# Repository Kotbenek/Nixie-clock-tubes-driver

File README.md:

# Moved to Codeberg

This repository was moved to Codeberg:
https://codeberg.org/Kotbenek/Nixie-clock-tubes-driver

# Nixie-clock-tubes-driver
PCB responsible for driving Nixie tubes

## Board overview

- 6P6C connector used for interfacing the [Nixie clock main board](https://github.com/Kotbenek/Nixie-clock-main-board)
- 180V DC input (powered by [180V power supply](https://github.com/Kotbenek/180V-power-supply))
- 6 11-pin connectors for 6 Nixie tubes:
  - 10 cathode pins, statically driving each digit
  - 1 anode pin, with dimming capability (PWM)

## Images

## External 3D models used in the PCB render

- [6P6C connector](https://grabcad.com/library/rj12-1)

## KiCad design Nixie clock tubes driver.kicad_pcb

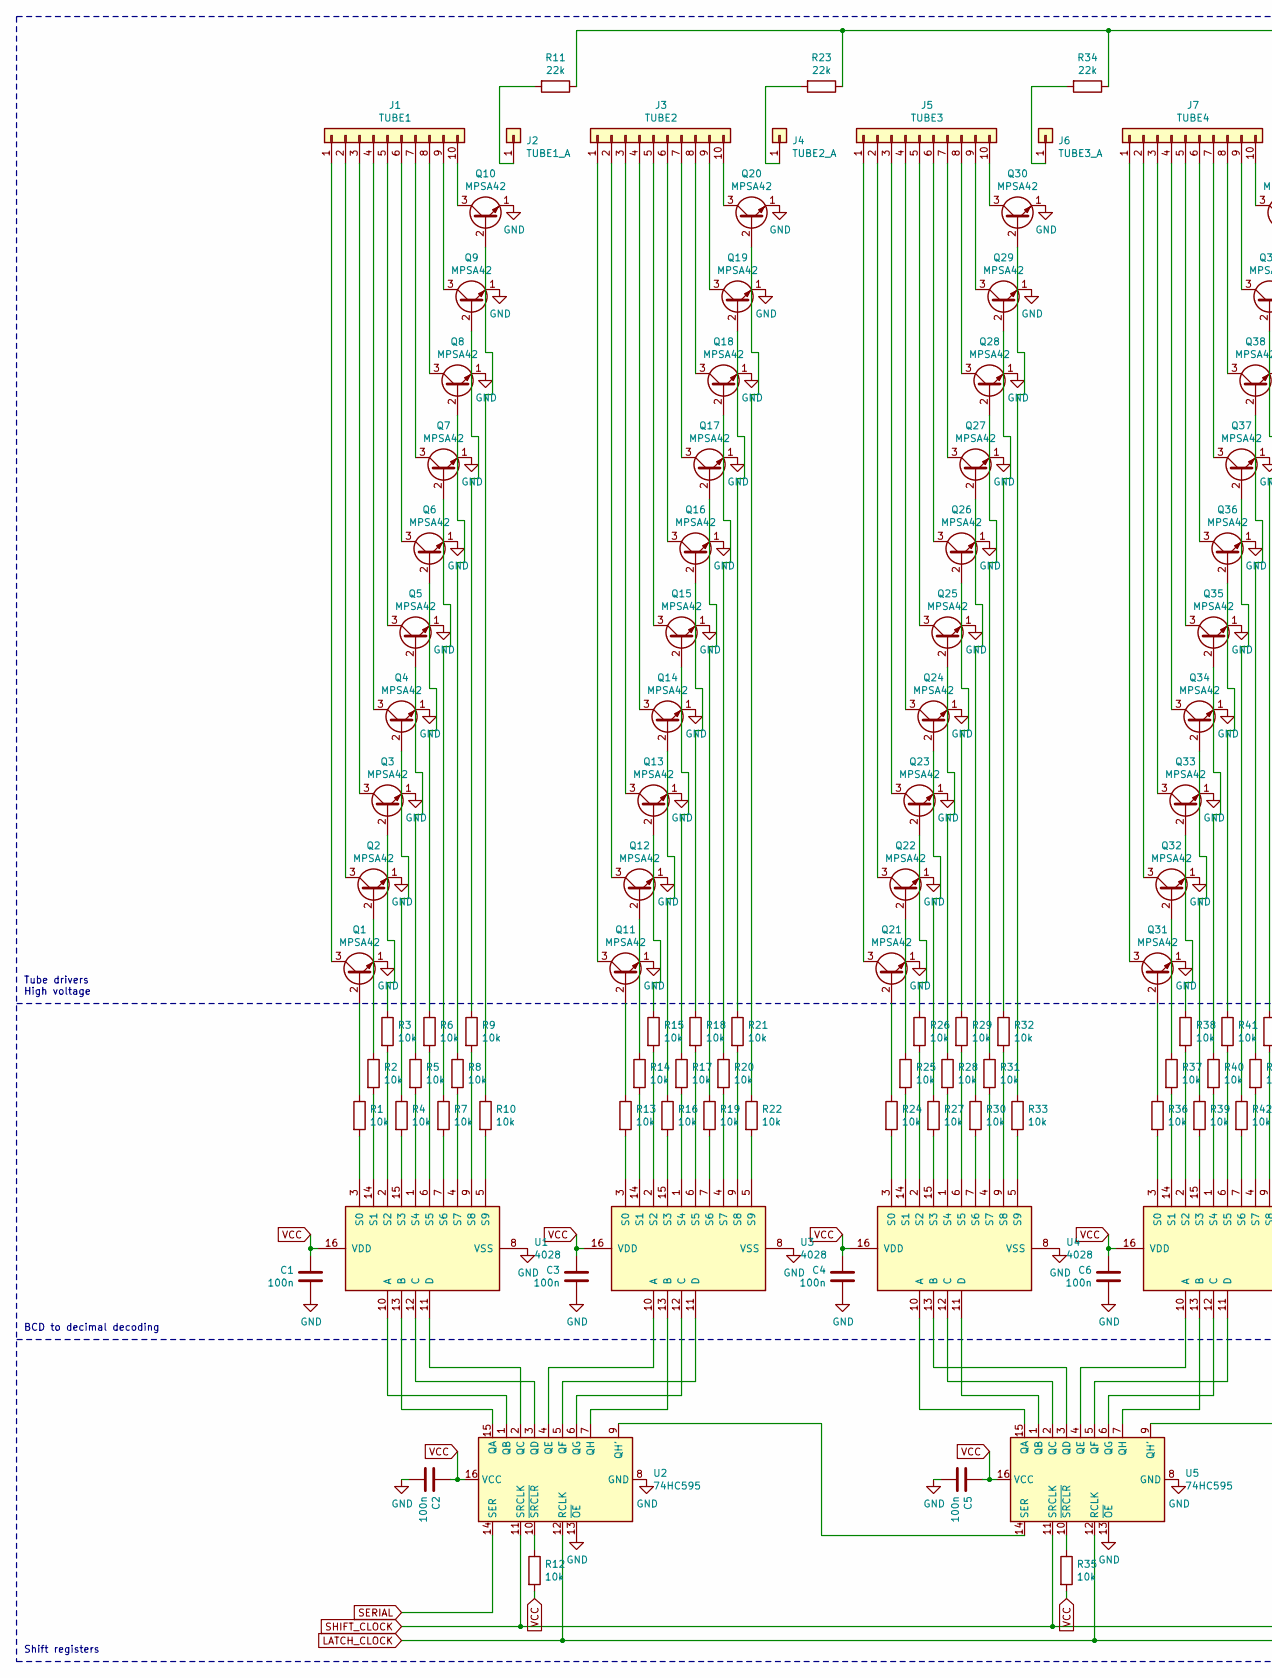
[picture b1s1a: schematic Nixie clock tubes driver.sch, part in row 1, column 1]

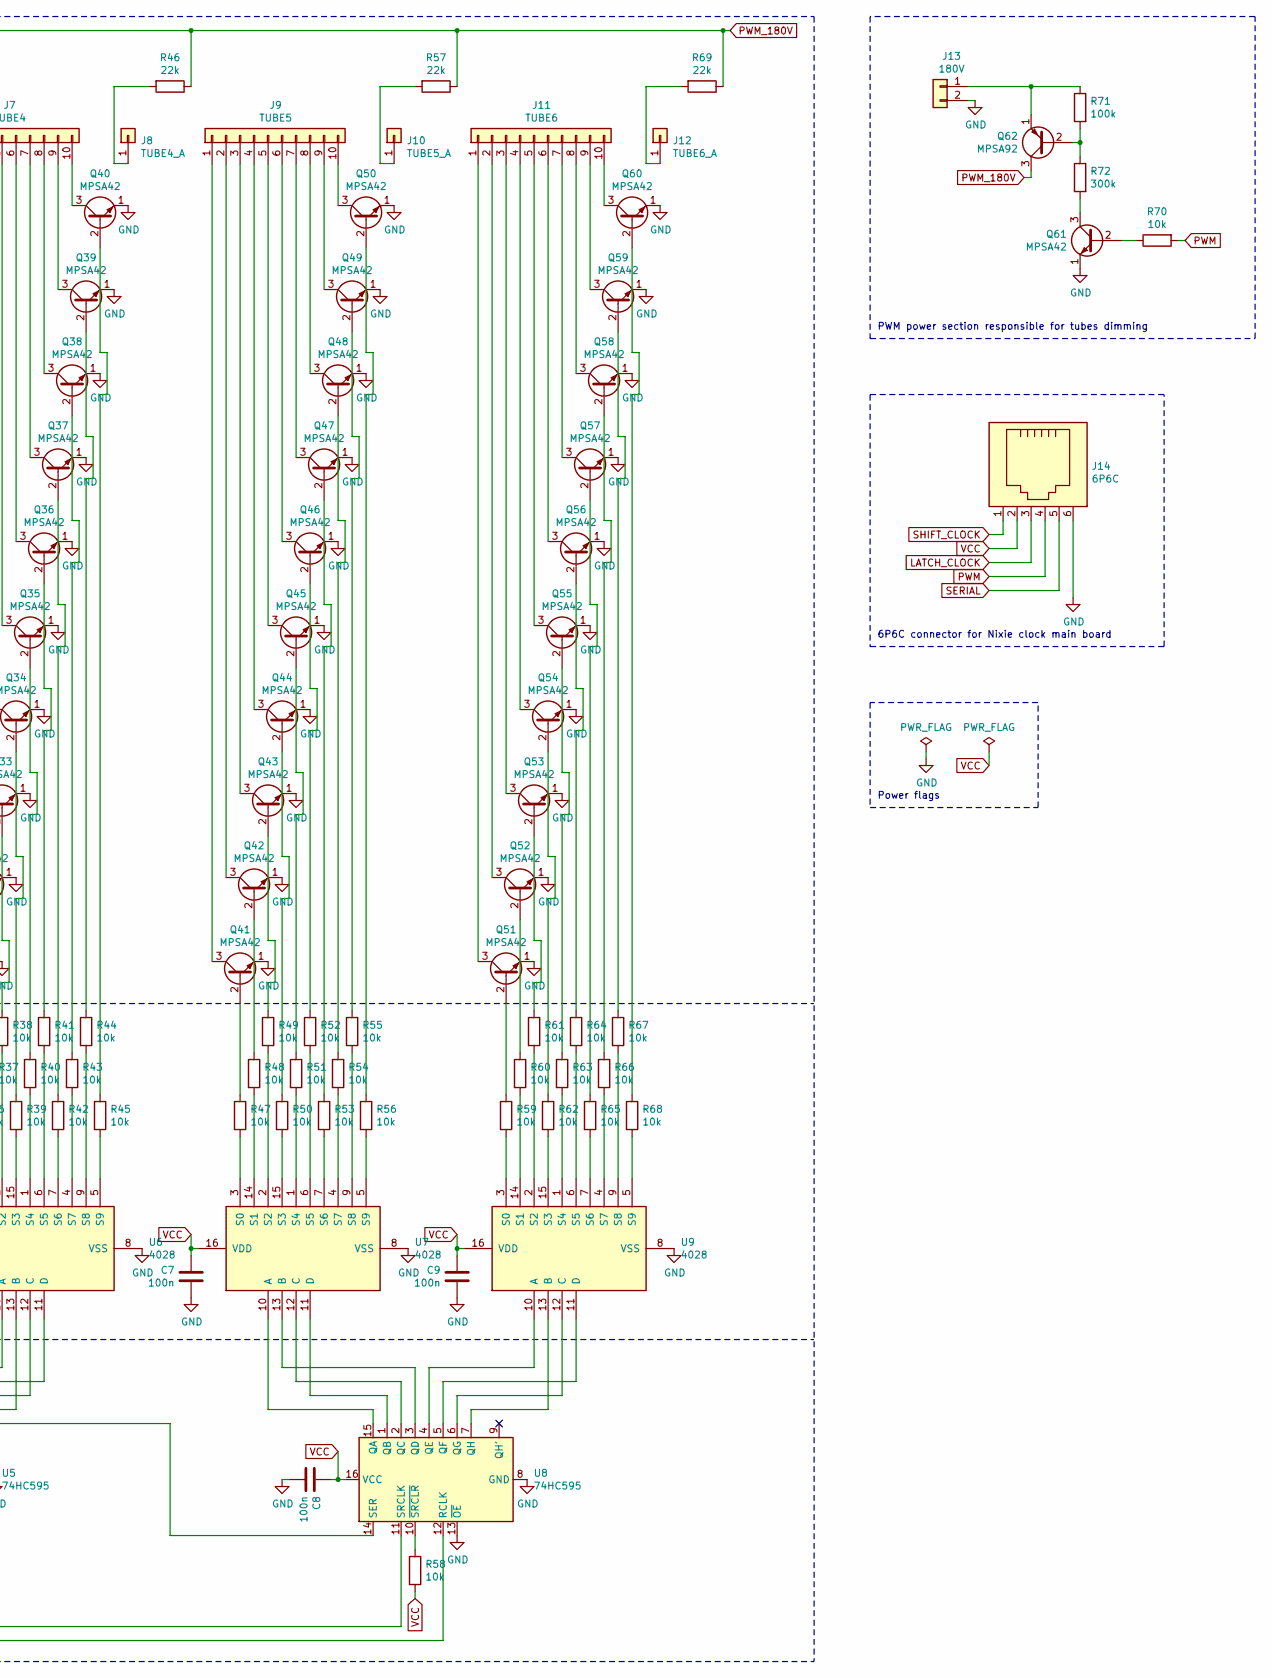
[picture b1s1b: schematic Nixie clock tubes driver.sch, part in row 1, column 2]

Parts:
C1, C2, C3, C4, C5, C6, C7, C8, C9: 100n; C_0805_2012Metric
J1: TUBE1; PinHeader_1x10_P2.54mm_Vertical
J2: TUBE1_A; PinHeader_1x01_P2.54mm_Vertical
J3: TUBE2; PinHeader_1x10_P2.54mm_Vertical
J4: TUBE2_A; PinHeader_1x01_P2.54mm_Vertical
J5: TUBE3; PinHeader_1x10_P2.54mm_Vertical
J6: TUBE3_A; PinHeader_1x01_P2.54mm_Vertical
J7: TUBE4; PinHeader_1x10_P2.54mm_Vertical
J8: TUBE4_A; PinHeader_1x01_P2.54mm_Vertical
J9: TUBE5; PinHeader_1x10_P2.54mm_Vertical
J10: TUBE5_A; PinHeader_1x01_P2.54mm_Vertical
J11: TUBE6; PinHeader_1x10_P2.54mm_Vertical
J12: TUBE6_A; PinHeader_1x01_P2.54mm_Vertical
J13: 180V; PinHeader_1x02_P2.54mm_Vertical
J14: 6P6C; RJ12_Amphenol_54601
Q1, Q2, Q3, Q4, Q5, Q6, Q7, Q8, Q9, Q10, Q11, Q12, Q13, Q14, Q15, Q16, Q17, Q18, Q19, Q20, Q21, Q22, Q23, Q24, Q25, Q26, Q27, Q28, Q29, Q30, Q31, Q32, Q33, Q34, Q35, Q36, Q37, Q38, Q39, Q40, Q41, Q42, Q43, Q44, Q45, Q46, Q47, Q48, Q49, Q50, Q51, Q52, Q53, Q54, Q55, Q56, Q57, Q58, Q59, Q60, Q61: MPSA42; TO-92_Inline
Q62: MPSA92; TO-92_Inline
R1, R2, R3, R4, R5, R6, R7, R8, R9, R10, R12, R13, R14, R15, R16, R17, R18, R19, R20, R21, R22, R24, R25, R26, R27, R28, R29, R30, R31, R32, R33, R35, R36, R37, R38, R39, R40, R41, R42, R43, R44, R45, R47, R48, R49, R50, R51, R52, R53, R54, R55, R56, R58, R59, R60, R61, R62, R63, R64, R65, R66, R67, R68, R70: 10k; R_0805_2012Metric
R11, R23, R34, R46, R57, R69: 22k; R_1206_3216Metric
R71: 100k; R_1206_3216Metric
R72: 300k; R_1206_3216Metric
U1, U3, U4, U6, U7, U9: 4028; SOIC-16_4.55x10.3mm_P1.27mm
U2, U5, U8: 74HC595; SOIC-16_4.55x10.3mm_P1.27mm

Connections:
GND: C1.2, C2.2, C3.2, C4.2, C5.2, C6.2, C7.2, C8.2, C9.2, J13.2, J14.6, Q1.1 (E), Q2.1 (E), Q3.1 (E), Q4.1 (E), Q5.1 (E), Q6.1 (E), Q7.1 (E), Q8.1 (E), Q9.1 (E), Q10.1 (E), Q11.1 (E), Q12.1 (E), Q13.1 (E), Q14.1 (E), Q15.1 (E), Q16.1 (E), Q17.1 (E), Q18.1 (E), Q19.1 (E), Q20.1 (E), Q21.1 (E), Q22.1 (E), Q23.1 (E), Q24.1 (E), Q25.1 (E), Q26.1 (E), Q27.1 (E), Q28.1 (E), Q29.1 (E), Q30.1 (E), Q31.1 (E), Q32.1 (E), Q33.1 (E), Q34.1 (E), Q35.1 (E), Q36.1 (E), Q37.1 (E), Q38.1 (E), Q39.1 (E), Q40.1 (E), Q41.1 (E), Q42.1 (E), Q43.1 (E), Q44.1 (E), Q45.1 (E), Q46.1 (E), Q47.1 (E), Q48.1 (E), Q49.1 (E), Q50.1 (E), Q51.1 (E), Q52.1 (E), Q53.1 (E), Q54.1 (E), Q55.1 (E), Q56.1 (E), Q57.1 (E), Q58.1 (E), Q59.1 (E), Q60.1 (E), Q61.1 (E), U1.8 (VSS), U2.8 (GND), U2.13 (~OE), U3.8 (VSS), U4.8 (VSS), U5.8 (GND), U5.13 (~OE), U6.8 (VSS), U7.8 (VSS), U8.8 (GND), U8.13 (~OE), U9.8 (VSS)
LATCH_CLOCK: J14.3, U2.12 (RCLK), U5.12 (RCLK), U8.12 (RCLK)
unnamed: J1.1, Q1.3 (C)
unnamed: J1.2, Q2.3 (C)
unnamed: J1.3, Q3.3 (C)
unnamed: J1.4, Q4.3 (C)
unnamed: J1.5, Q5.3 (C)
unnamed: J1.6, Q6.3 (C)
unnamed: J1.7, Q7.3 (C)
unnamed: J1.8, Q8.3 (C)
unnamed: J1.9, Q9.3 (C)
unnamed: J1.10, Q10.3 (C)
unnamed: J2.1, R11.2
unnamed: J3.1, Q11.3 (C)
unnamed: J3.2, Q12.3 (C)
unnamed: J3.3, Q13.3 (C)
unnamed: J3.4, Q14.3 (C)
unnamed: J3.5, Q15.3 (C)
unnamed: J3.6, Q16.3 (C)
unnamed: J3.7, Q17.3 (C)
unnamed: J3.8, Q18.3 (C)
unnamed: J3.9, Q19.3 (C)
unnamed: J3.10, Q20.3 (C)
unnamed: J4.1, R23.2
unnamed: J5.1, Q21.3 (C)
unnamed: J5.2, Q22.3 (C)
unnamed: J5.3, Q23.3 (C)
unnamed: J5.4, Q24.3 (C)
unnamed: J5.5, Q25.3 (C)
unnamed: J5.6, Q26.3 (C)
unnamed: J5.7, Q27.3 (C)
unnamed: J5.8, Q28.3 (C)
unnamed: J5.9, Q29.3 (C)
unnamed: J5.10, Q30.3 (C)
unnamed: J6.1, R34.2
unnamed: J7.1, Q31.3 (C)
unnamed: J7.2, Q32.3 (C)
unnamed: J7.3, Q33.3 (C)
unnamed: J7.4, Q34.3 (C)
unnamed: J7.5, Q35.3 (C)
unnamed: J7.6, Q36.3 (C)
unnamed: J7.7, Q37.3 (C)
unnamed: J7.8, Q38.3 (C)
unnamed: J7.9, Q39.3 (C)
unnamed: J7.10, Q40.3 (C)
unnamed: J8.1, R46.2
unnamed: J9.1, Q41.3 (C)
unnamed: J9.2, Q42.3 (C)
unnamed: J9.3, Q43.3 (C)
unnamed: J9.4, Q44.3 (C)
unnamed: J9.5, Q45.3 (C)
unnamed: J9.6, Q46.3 (C)
unnamed: J9.7, Q47.3 (C)
unnamed: J9.8, Q48.3 (C)
unnamed: J9.9, Q49.3 (C)
unnamed: J9.10, Q50.3 (C)
unnamed: J10.1, R57.2
unnamed: J11.1, Q51.3 (C)
unnamed: J11.2, Q52.3 (C)
unnamed: J11.3, Q53.3 (C)
unnamed: J11.4, Q54.3 (C)
unnamed: J11.5, Q55.3 (C)
unnamed: J11.6, Q56.3 (C)
unnamed: J11.7, Q57.3 (C)
unnamed: J11.8, Q58.3 (C)
unnamed: J11.9, Q59.3 (C)
unnamed: J11.10, Q60.3 (C)
unnamed: J12.1, R69.2
unnamed: J13.1, Q62.1 (E), R71.1
unnamed: Q1.2 (B), R1.1
unnamed: Q2.2 (B), R2.1
unnamed: Q3.2 (B), R3.1
unnamed: Q4.2 (B), R4.1
unnamed: Q5.2 (B), R5.1
unnamed: Q6.2 (B), R6.1
unnamed: Q7.2 (B), R7.1
unnamed: Q8.2 (B), R8.1
unnamed: Q9.2 (B), R9.1
unnamed: Q10.2 (B), R10.1
unnamed: Q11.2 (B), R13.1
unnamed: Q12.2 (B), R14.1
unnamed: Q13.2 (B), R15.1
unnamed: Q14.2 (B), R16.1
unnamed: Q15.2 (B), R17.1
unnamed: Q16.2 (B), R18.1
unnamed: Q17.2 (B), R19.1
unnamed: Q18.2 (B), R20.1
unnamed: Q19.2 (B), R21.1
unnamed: Q20.2 (B), R22.1
unnamed: Q21.2 (B), R24.1
unnamed: Q22.2 (B), R25.1
unnamed: Q23.2 (B), R26.1
unnamed: Q24.2 (B), R27.1
unnamed: Q25.2 (B), R28.1
unnamed: Q26.2 (B), R29.1
unnamed: Q27.2 (B), R30.1
unnamed: Q28.2 (B), R31.1
unnamed: Q29.2 (B), R32.1
unnamed: Q30.2 (B), R33.1
unnamed: Q31.2 (B), R36.1
unnamed: Q32.2 (B), R37.1
unnamed: Q33.2 (B), R38.1
unnamed: Q34.2 (B), R39.1
unnamed: Q35.2 (B), R40.1
unnamed: Q36.2 (B), R41.1
unnamed: Q37.2 (B), R42.1
unnamed: Q38.2 (B), R43.1
unnamed: Q39.2 (B), R44.1
unnamed: Q40.2 (B), R45.1
unnamed: Q41.2 (B), R47.1
unnamed: Q42.2 (B), R48.1
unnamed: Q43.2 (B), R49.1
unnamed: Q44.2 (B), R50.1
unnamed: Q45.2 (B), R51.1
unnamed: Q46.2 (B), R52.1
unnamed: Q47.2 (B), R53.1
unnamed: Q48.2 (B), R54.1
unnamed: Q49.2 (B), R55.1
unnamed: Q50.2 (B), R56.1
unnamed: Q51.2 (B), R59.1
unnamed: Q52.2 (B), R60.1
unnamed: Q53.2 (B), R61.1
unnamed: Q54.2 (B), R62.1
unnamed: Q55.2 (B), R63.1
unnamed: Q56.2 (B), R64.1
unnamed: Q57.2 (B), R65.1
unnamed: Q58.2 (B), R66.1
unnamed: Q59.2 (B), R67.1
unnamed: Q60.2 (B), R68.1
unnamed: Q61.2 (B), R70.1
unnamed: Q61.3 (C), R72.2
unnamed: Q62.2 (B), R71.2, R72.1
unnamed: R1.2, U1.3 (S0)
unnamed: R2.2, U1.14 (S1)
unnamed: R3.2, U1.2 (S2)
unnamed: R4.2, U1.15 (S3)
unnamed: R5.2, U1.1 (S4)
unnamed: R6.2, U1.6 (S5)
unnamed: R7.2, U1.7 (S6)
unnamed: R8.2, U1.4 (S7)
unnamed: R9.2, U1.9 (S8)
unnamed: R10.2, U1.5 (S9)
unnamed: R12.1, U2.10 (~SRCLR)
unnamed: R13.2, U3.3 (S0)
unnamed: R14.2, U3.14 (S1)
unnamed: R15.2, U3.2 (S2)
unnamed: R16.2, U3.15 (S3)
unnamed: R17.2, U3.1 (S4)
unnamed: R18.2, U3.6 (S5)
unnamed: R19.2, U3.7 (S6)
unnamed: R20.2, U3.4 (S7)
unnamed: R21.2, U3.9 (S8)
unnamed: R22.2, U3.5 (S9)
unnamed: R24.2, U4.3 (S0)
unnamed: R25.2, U4.14 (S1)
unnamed: R26.2, U4.2 (S2)
unnamed: R27.2, U4.15 (S3)
unnamed: R28.2, U4.1 (S4)
unnamed: R29.2, U4.6 (S5)
unnamed: R30.2, U4.7 (S6)
unnamed: R31.2, U4.4 (S7)
unnamed: R32.2, U4.9 (S8)
unnamed: R33.2, U4.5 (S9)
unnamed: R35.1, U5.10 (~SRCLR)
unnamed: R36.2, U6.3 (S0)
unnamed: R37.2, U6.14 (S1)
unnamed: R38.2, U6.2 (S2)
unnamed: R39.2, U6.15 (S3)
unnamed: R40.2, U6.1 (S4)
unnamed: R41.2, U6.6 (S5)
unnamed: R42.2, U6.7 (S6)
unnamed: R43.2, U6.4 (S7)
unnamed: R44.2, U6.9 (S8)
unnamed: R45.2, U6.5 (S9)
unnamed: R47.2, U7.3 (S0)
unnamed: R48.2, U7.14 (S1)
unnamed: R49.2, U7.2 (S2)
unnamed: R50.2, U7.15 (S3)
unnamed: R51.2, U7.1 (S4)
unnamed: R52.2, U7.6 (S5)
unnamed: R53.2, U7.7 (S6)
unnamed: R54.2, U7.4 (S7)
unnamed: R55.2, U7.9 (S8)
unnamed: R56.2, U7.5 (S9)
unnamed: R58.1, U8.10 (~SRCLR)
unnamed: R59.2, U9.3 (S0)
unnamed: R60.2, U9.14 (S1)
unnamed: R61.2, U9.2 (S2)
unnamed: R62.2, U9.15 (S3)
unnamed: R63.2, U9.1 (S4)
unnamed: R64.2, U9.6 (S5)
unnamed: R65.2, U9.7 (S6)
unnamed: R66.2, U9.4 (S7)
unnamed: R67.2, U9.9 (S8)
unnamed: R68.2, U9.5 (S9)
unnamed: U1.10 (A), U2.1 (QB)
unnamed: U1.11 (D), U2.2 (QC)
unnamed: U1.12 (C), U2.3 (QD)
unnamed: U1.13 (B), U2.15 (QA)
unnamed: U2.4 (QE), U3.10 (A)
unnamed: U2.5 (QF), U3.11 (D)
unnamed: U2.6 (QG), U3.12 (C)
unnamed: U2.7 (QH), U3.13 (B)
unnamed: U2.9 (QH'), U5.14 (SER)
unnamed: U4.10 (A), U5.15 (QA)
unnamed: U4.11 (D), U5.1 (QB)
unnamed: U4.12 (C), U5.2 (QC)
unnamed: U4.13 (B), U5.3 (QD)
unnamed: U5.4 (QE), U6.10 (A)
unnamed: U5.5 (QF), U6.11 (D)
unnamed: U5.6 (QG), U6.12 (C)
unnamed: U5.7 (QH), U6.13 (B)
unnamed: U5.9 (QH'), U8.14 (SER)
unnamed: U7.10 (A), U8.15 (QA)
unnamed: U7.11 (D), U8.1 (QB)
unnamed: U7.12 (C), U8.2 (QC)
unnamed: U7.13 (B), U8.3 (QD)
unnamed: U8.4 (QE), U9.10 (A)
unnamed: U8.5 (QF), U9.11 (D)
unnamed: U8.6 (QG), U9.12 (C)
unnamed: U8.7 (QH), U9.13 (B)
PWM: J14.4, R70.2
PWM_180V: Q62.3 (C), R11.1, R23.1, R34.1, R46.1, R57.1, R69.1
SERIAL: J14.5, U2.14 (SER)
SHIFT_CLOCK: J14.1, U2.11 (SRCLK), U5.11 (SRCLK), U8.11 (SRCLK)
VCC: C1.1, C2.1, C3.1, C4.1, C5.1, C6.1, C7.1, C8.1, C9.1, J14.2, R12.2, R35.2, R58.2, U1.16 (VDD), U2.16 (VCC), U3.16 (VDD), U4.16 (VDD), U5.16 (VCC), U6.16 (VDD), U7.16 (VDD), U8.16 (VCC), U9.16 (VDD)

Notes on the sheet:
6P6C connector for Nixie clock main board
PWM power section responsible for tubes dimming
Shift registers
Tube drivers High voltage
BCD to decimal decoding
Power flags

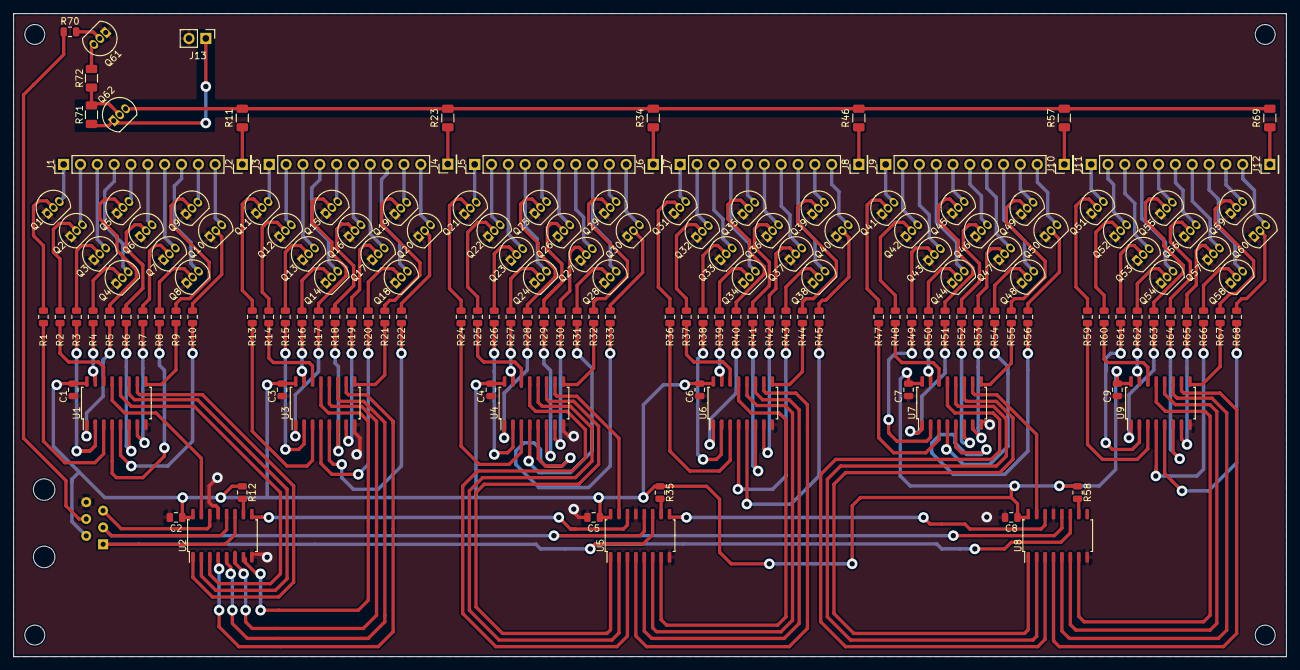
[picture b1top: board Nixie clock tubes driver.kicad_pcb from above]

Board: 2 copper layers, 192.0 x 97.0 mm, 166 parts (0 on the bottom side), 226 nets.

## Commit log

2021-02-05 Version 1.0
2021-02-05 Added README.md and PCB images
2021-02-05 Added gerber files
2021-02-05 Added schematic as pdf file
2021-04-22 Added LICENSE.md
2021-09-03 Added missing gerber files
2024-09-25 LICENSE.md: Change line breaks from CRLF to LF
2024-09-25 LICENSE.md: Update date
2025-08-17 Moved to Codeberg
